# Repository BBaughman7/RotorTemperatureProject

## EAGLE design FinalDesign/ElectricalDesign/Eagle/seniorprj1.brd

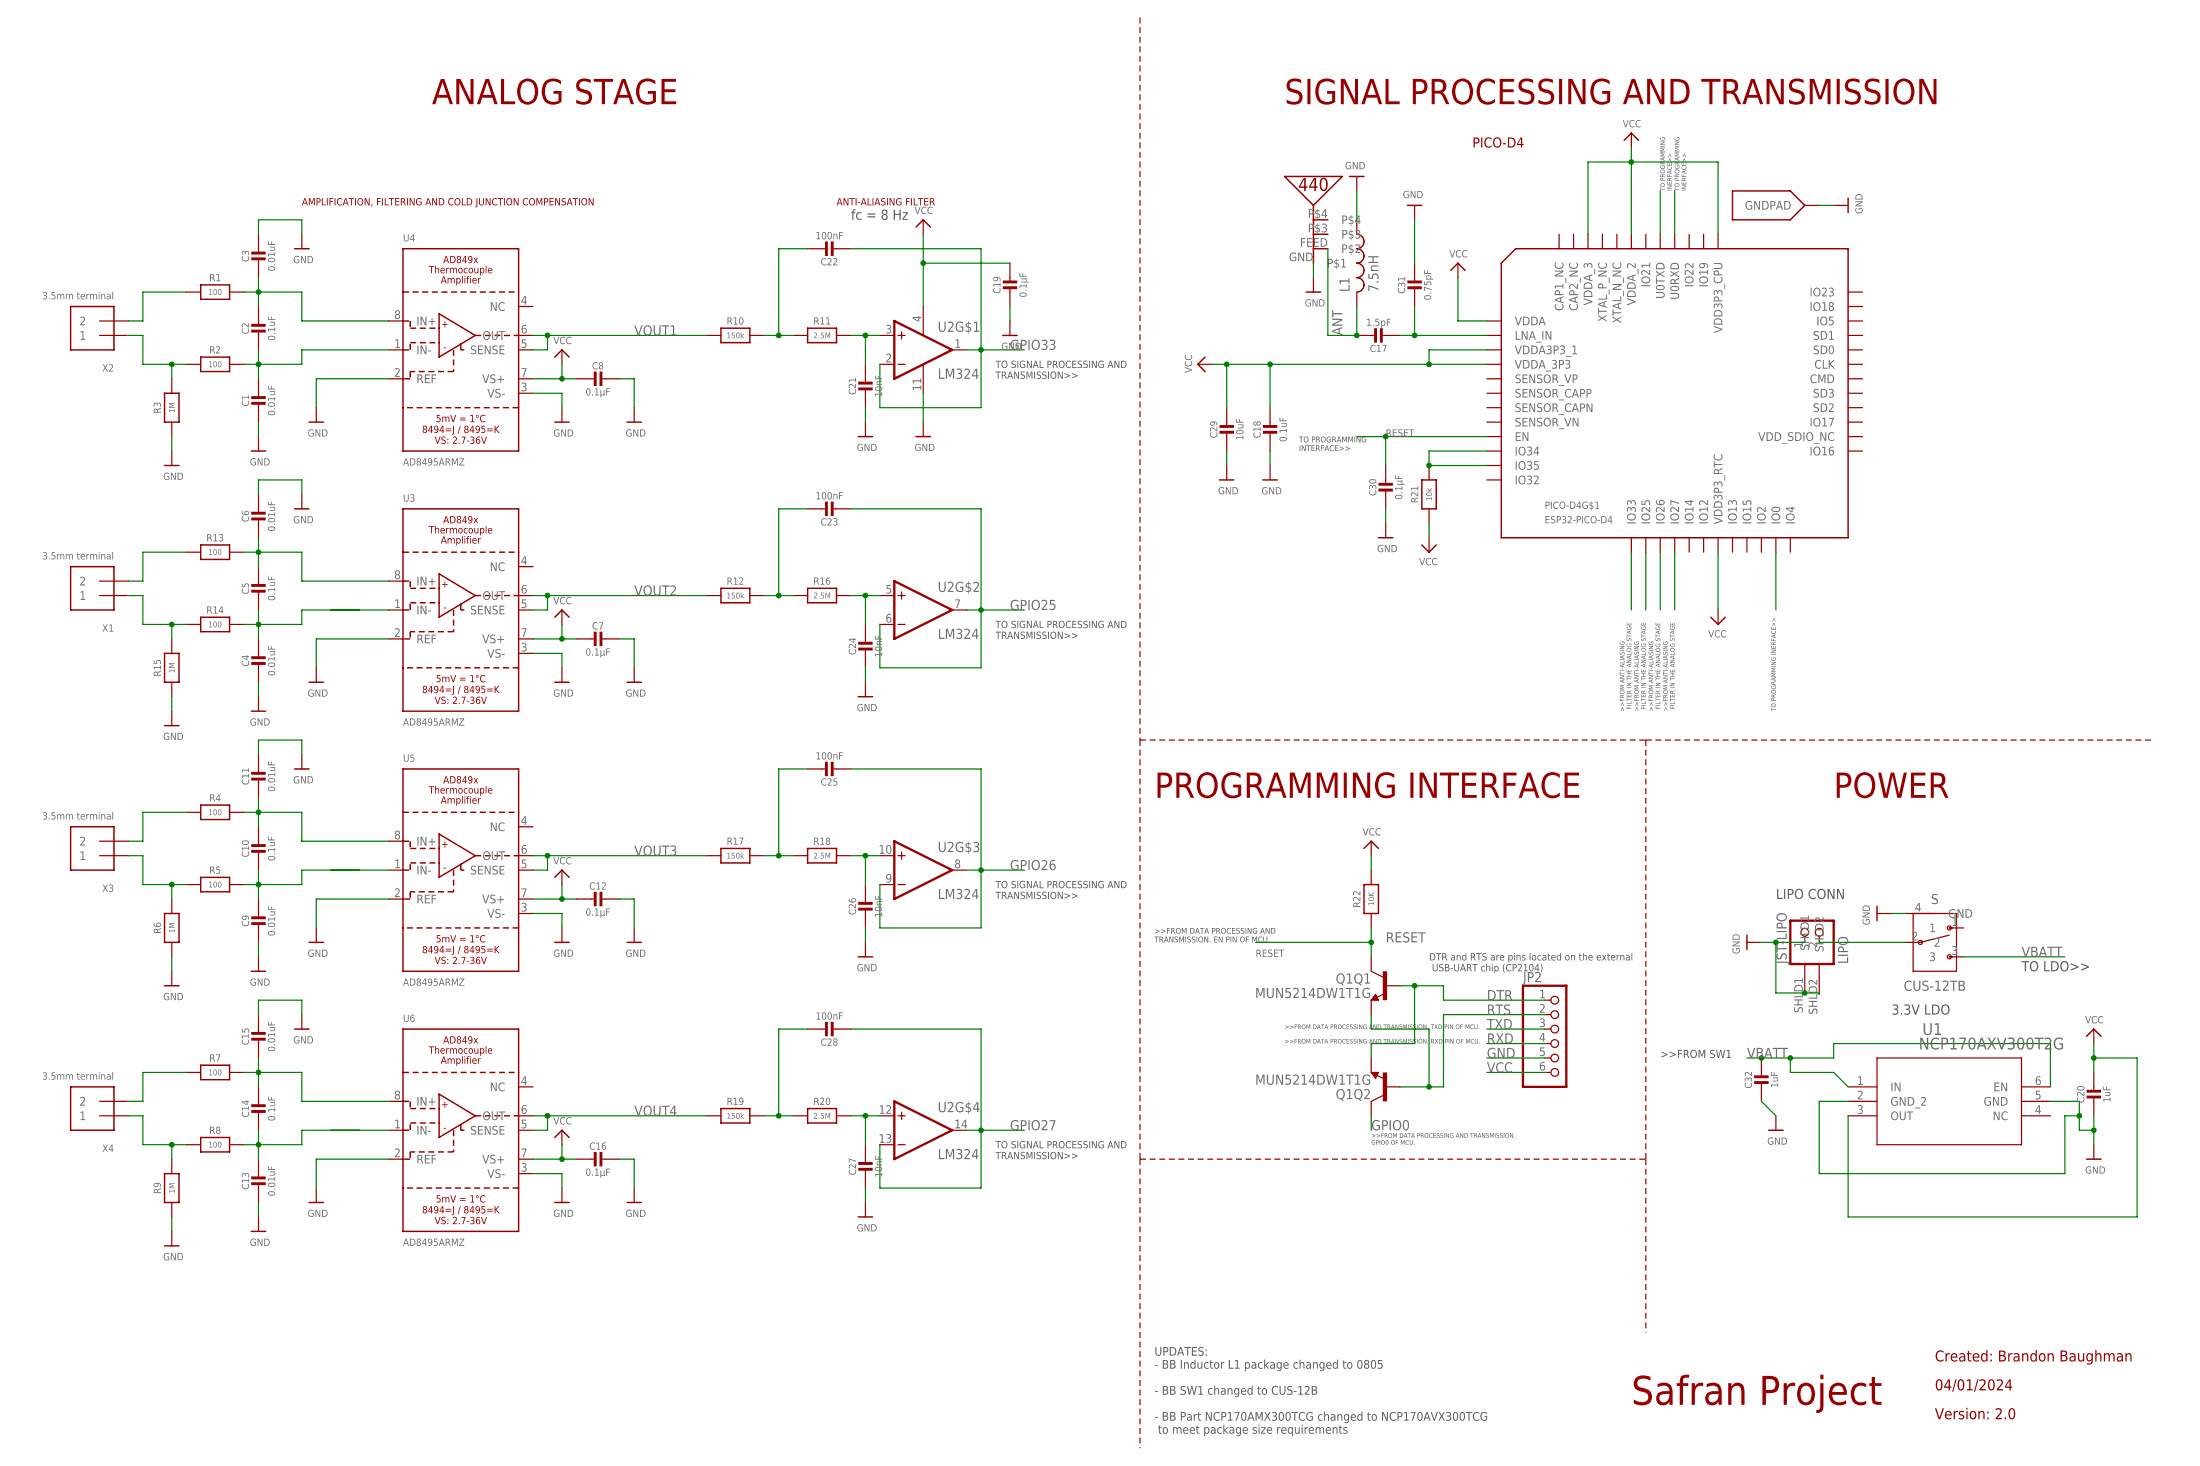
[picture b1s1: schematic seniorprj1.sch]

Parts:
C1, C3, C4, C6, C9, C11, C13, C15: 0.01uF; 0805-NO@1; MPN R76PD2100SE30J
C2, C5, C10, C14, C18: 0.1uF; 0805-NO@1; MPN C0805C104K1RECTU
C7, C8, C12, C16, C19, C30: 0.1µF; 0805-NO@1; MPN C0805C104K1RECTU
C17: 1.5pF; 0805-NO@1; MPN CC0805CRNPO9BN1R5
C20, C32: 1uF; 0805-NO@1; MPN 08051C105K4T2A
C21, C24, C26, C27: 10nF; 0805-NO@1; MPN C0805C103K1RECTU
C22, C23, C25, C28: 100nF; 0805-NO@1; MPN C0805C104K1RECTU
C29: 10uF; 0805-NO@1; MPN C0805C106J8RACAUTO
C31: 0.75pF; 0805-NO@1
JP2: PINHD-1X6; 1X06; MPN 826631-6
JST-LIPO: LIPO; JSTPH2
L1: 7.5nH; RESC0805_N; MPN BSPQ000603047N5H00
PICO-D4: ESP32-PICO-D4; PICO-D4-QFN48
Q1: MUN5214DW1T1G; DUAL_NPN_SC70-6; MPN MUN5214DW1T1G
R1, R2, R4, R5, R7, R8, R13, R14: 100; 0805-NO; MPN CRCW0805100RFKTA
R3, R6, R9, R15: 1M; 0805-NO; MPN ERJ-P06J105V
R10, R12, R17, R19: 150k; 0805-NO; MPN CRCW0805150KFKEA
R11, R16, R18, R20: 2.5M; 0805-NO
R21: 10k; 0805-NO; MPN RC0805FR-0710KL
R22: 10K; 0805-NO; MPN RC0805FR-0710KL
S: CUS-12TB; CUS-12B
U1: NCP170AXV300T2G; SOT-563_1P3X1P7_ONS
U2: LM324; SOIC127P600X175-14N; MPN LM324N/NOPB
U3, U4, U5, U6: AD8495ARMZ; MSOP8_0.65MM; MPN AD8495ARMZ-R7
U$35: PRO-OB-440
X1, X2, X3, X4: 3.5mm terminal; TERMBLOCK_1X2-3.5MM; MPN MA212-350M02

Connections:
ANT: C17.1, L1.2, U$35.FEED
DTR: JP2.1, Q1.1 (E), Q1.5 (B)
GND: C1.2, C3.1, C4.2, C6.1, C7.1, C8.1, C9.2, C11.1, C12.1, C13.2, C15.1, C16.1, C18.2, C19.2, C20.2, C21.2, C24.2, C26.2, C27.2, C29.2, C30.2, C31.1, C32.2, JP2.5, JST-LIPO.1, JST-LIPO.SHLD1, JST-LIPO.SHLD2, L1.1, PICO-D4.EXP (GNDPAD), R3.1, R6.1, R9.1, R15.1, S.4 (GND), U1.2 (GND_2), U1.5 (GND), U2.11 (VCC-), U3.2 (REF), U3.3 (VS-), U4.2 (REF), U4.3 (VS-), U5.2 (REF), U5.3 (VS-), U6.2 (REF), U6.3 (VS-), U$35.GND
GPIO0: PICO-D4.23 (IO0), Q1.6 (C)
GPIO25: C23.2, U2.6 (INVERTING_INPUT2), U2.7 (OUTPUT2)
GPIO26: C25.2, U2.8 (OUTPUT3), U2.9 (INVERTING_INPUT3)
GPIO27: C28.2, U2.13 (INVERTING_INPUT4), U2.14 (OUTPUT4)
GPIO33: C22.2, U2.1 (OUTPUT1), U2.2 (INVERTING_INPUT1)
IN+: R13.1, X1.2
IN+1: R1.1, X2.2
IN+2: R4.1, X3.2
IN+3: R7.1, X4.2
IN-: R14.1, R15.2, X1.1
IN-1: R2.1, R3.2, X2.1
IN-2: R5.1, R6.2, X3.1
IN-3: R8.1, R9.2, X4.1
IO12: PICO-D4.18 (IO12)
IO21: PICO-D4.42 (IO21)
LNA_IN: C17.2, C31.2, PICO-D4.2 (LNA_IN)
unnamed: C2.1, C3.2, R1.2, U4.8 (IN+)
unnamed: C5.1, C6.2, R13.2, U3.8 (IN+)
unnamed: C4.1, C5.2, R14.2
unnamed: C1.1, C2.2, R2.2, U4.1 (IN-)
unnamed: C10.1, C11.2, R4.2, U5.8 (IN+)
unnamed: C9.1, C10.2, R5.2
unnamed: C14.1, C15.2, R7.2, U6.8 (IN+)
unnamed: C13.1, C14.2, R8.2
unnamed: JST-LIPO.2, S.2
unnamed: C22.1, R10.2, R11.1
unnamed: C21.1, R11.2, U2.3 (NON-INVERTING_INPUT1)
unnamed: C24.1, R16.2, U2.5 (NON-INVERTING_INPUT2)
unnamed: C23.1, R12.2, R16.1
unnamed: C25.1, R17.2, R18.1
unnamed: C28.1, R19.2, R20.1
unnamed: C26.1, R18.2, U2.10 (NON-INVERTING_INPUT3)
unnamed: C27.1, R20.2, U2.12 (NON-INVERTING_INPUT4)
unnamed: PICO-D4.10 (IO34), PICO-D4.11 (IO35), R21.2
RESET: C30.1, PICO-D4.9 (EN), Q1.3 (C), R22.1
RTS: JP2.2, Q1.2 (B), Q1.4 (E)
RXD: JP2.4, PICO-D4.40 (U0RXD)
SENSOR_CAPN: PICO-D4.7 (SENSOR_CAPN)
TXD: JP2.3, PICO-D4.41 (U0TXD)
VBATT: C32.1, S.3, U1.1 (IN), U1.6 (EN)
VCC: C7.2, C8.2, C12.2, C16.2, C18.1, C19.1, C20.1, C29.1, JP2.6, PICO-D4.1 (VDDA), PICO-D4.3 (VDDA3P3_1), PICO-D4.4 (VDDA_3P3), PICO-D4.19 (VDD3P3_RTC), PICO-D4.37 (VDD3P3_CPU), PICO-D4.43 (VDDA_2), PICO-D4.46 (VDDA_3), R21.1, R22.2, U1.3 (OUT), U2.4 (VCC+), U3.7 (VS+), U4.7 (VS+), U5.7 (VS+), U6.7 (VS+)
VOUT1: R10.1, U4.5 (SENSE), U4.6 (OUT)
VOUT2: R12.1, U3.5 (SENSE), U3.6 (OUT)
VOUT3: R17.1, U5.5 (SENSE), U5.6 (OUT)
VOUT4: R19.1, U6.5 (SENSE), U6.6 (OUT)

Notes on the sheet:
LIPO CONN
Created: Brandon Baughman
Safran Project
04/01/2024
Version: 2.0
PICO-D4
ANALOG STAGE
PROGRAMMING INTERFACE
POWER
SIGNAL PROCESSING AND TRANSMISSION
UPDATES: - BB Inductor L1 package changed to 0805 - BB SW1 changed to CUS-12B - BB Part NCP170AMX300TCG changed to NCP170AVX300TCG to meet package size requirements
DTR and RTS are pins located on the external USB-UART chip (CP2104)
AMPLIFICATION, FILTERING AND COLD JUNCTION COMPENSATION
ANTI-ALIASING FILTER
TO SIGNAL PROCESSING AND TRANSMISSION>>
TO PROGRAMMING INERFACE>>
TO PROGRAMMING INTERFACE>>
TO PROGRAMMING INERFACE>>
TO LDO>>
3.3V LDO
fc = 8 Hz

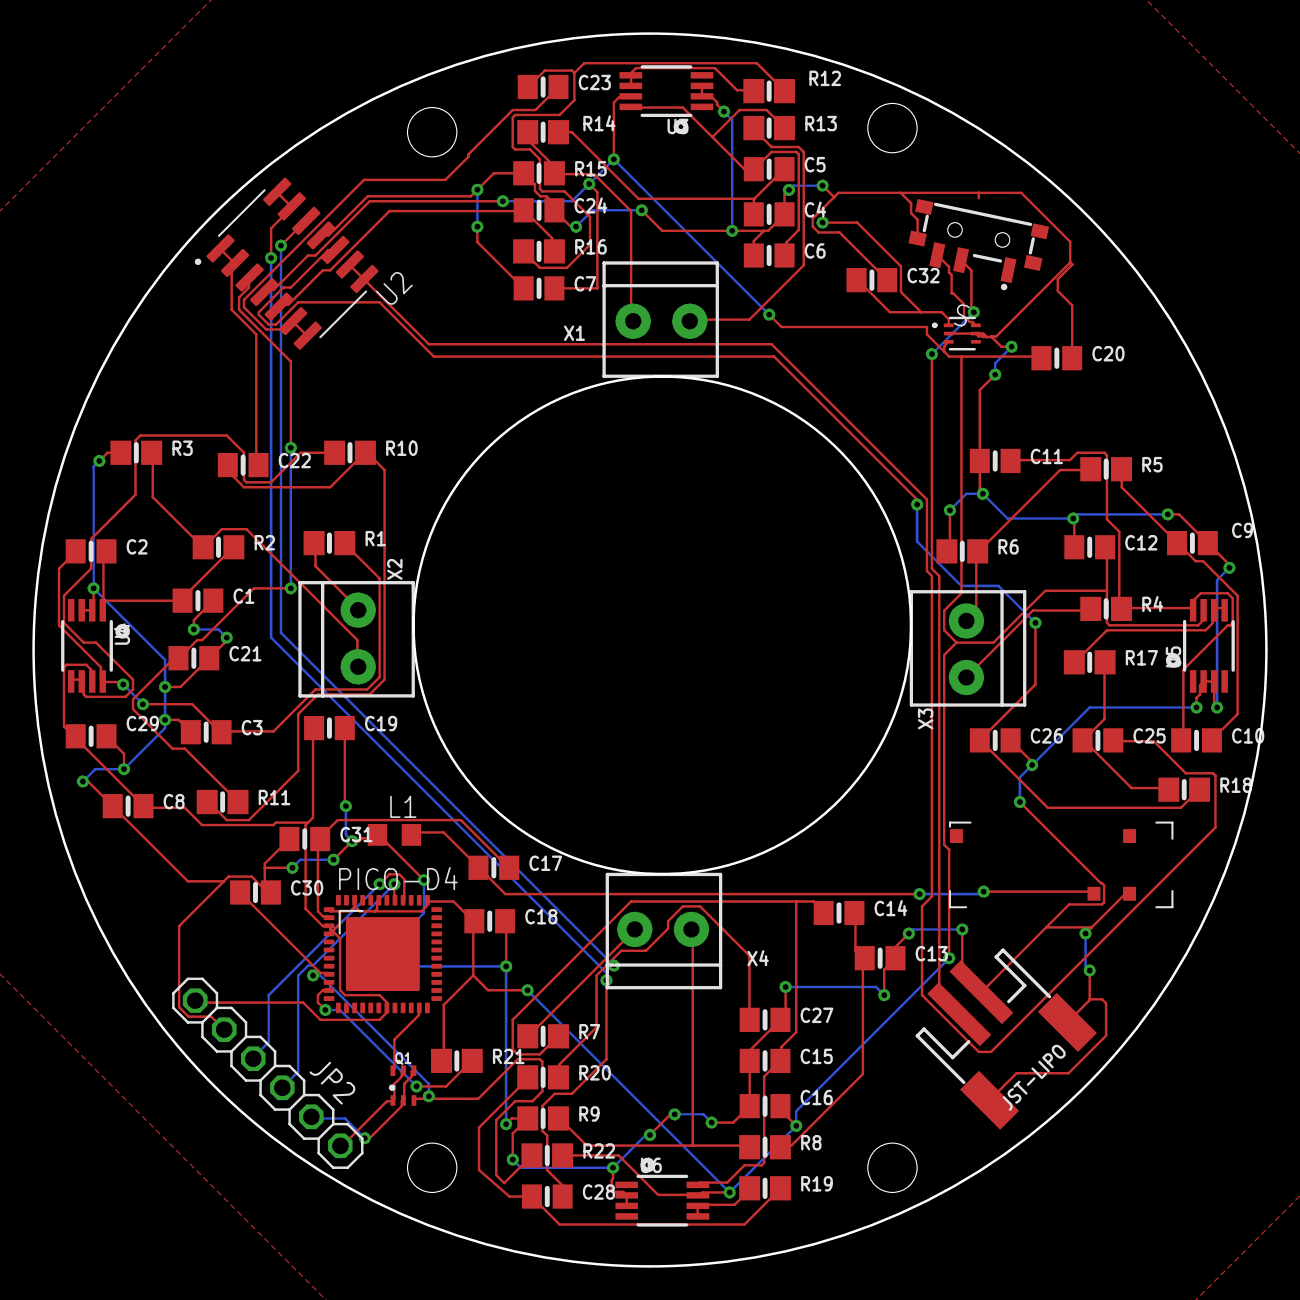
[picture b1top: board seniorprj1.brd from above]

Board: 2 copper layers, 76.2 x 76.2 mm, 71 parts (0 on the bottom side), 45 nets.

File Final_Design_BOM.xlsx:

Comment | Designator | Footprint | JLCPCB Part #（optional） | MFR Part# | Link to Part
0.01uF | C1,C3,C4,C6,C9,C11,C13,C15,C21,C24,C26,C27 | 0805 | C2971995 | 0805CG103J500NT | Link
0.1uF | C2,C5,C7,C8,C10,C12,C14,C16,C18,C19,C22,C23,C25,C28,C30 | 0805 | C2169476 | GCD21BR72A104KA01L | Link
0.75pF | C31 | 0805 | C519950 | CC0805CRNPO9BNR75 | Link
1uF | C20,C32 | 0805 | C89378 | 0805F105M250NT | Link
1.5pF | C17 | 0805 | C376869 | TCC0805COG1R5C500BT | Link
10uF | C29 | 0805 | C17024 | CL21A106KPFNNNE | Link
7.5nH | L1 | 0805 | C162658 | LQW2BAS7N5J00L | Link
2.5M Ohm | R11,R16,R18,R20 | 0805 | C153398 | TR0805D2M5P0515 | Link
1M Ohm | R3,R6,R9,R15 | 0805 | C881016 | CR0805F1M00P05Z | Link
150k Ohm | R10,R12,R17,R19 | 0805 | C276119 | RK73B2ATTD154J | Link
10k Ohm | R21,R22 | 0805 | C2912585 | HoAR0805-1/8W-10KR-0.1%-TCR25 | Link
100 Ohm | R1,R2,R4,R5,R7,R8,R13,R14 | 0805 | C346733 | RTAN0805BKE100R | Link
ESP32-PICO-D4 | PICO-D4 | QFN-48-EP(7x7) | C193707 | ESP32-PICO-D4 | Link
CUS-12TB | S | SMD | C2921739 | CUS-12TB | Link
LM324AMX/NOPB | U2 | SOIC-14 | C2057290 | LM324AMX/NOPB | Link
NCP170AXV300T2G | U1 | SOT-563 | C463131 | NCP170AXV300T2G | Link
PRO-OB-440 | U$35 | SMD | C5122736 | PRO-OB-440 | Link
MUN5214DW1T1G | Q1 | SOT-363 | C94403 | MUN5214DW1T1G | Link
S2B-PH-SM4-TB(LF)(SN) | JST-LIPO | SMD,P=2mm | C295747 | S2B-PH-SM4-TB(LF)(SN) | Link
AD8495ARMZ-R7 | U3,U4,U5,U6 | MSOP-8 | C59658 | AD8495ARMZ-R7 | Link
MF254V-11-06-1000-H70 | JP2 | Plugin,P=2.54mm | C2848407 | MF254V-11-06-1000-H70 | Link
DB301V-3.5-2P-GN-S | X1,X2,X3,X4 | Plugin,P=3.5mm | C695629 | DB301V-3.5-2P-GN-S | Link

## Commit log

2024-04-30 Create BOm
2024-04-30 Create eagle
2024-04-30 Create hard
2024-04-30 Create e
2024-04-30 Create a
2024-04-30 Create l
2024-04-30 Create p

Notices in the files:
parts and their libraries:
microbuilder: This work is placed in the public domain, and may be freely used for commercial and non-commercial work with the following conditions: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
COPYRIGHT: Copyright (C) 2024 Ultra Librarian. All rights reserved.
